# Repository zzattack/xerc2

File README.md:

Clone of XERC2 IR board for OG xbox.
Resembles original Sickmods design. Adds a programming header for the microcontroller.

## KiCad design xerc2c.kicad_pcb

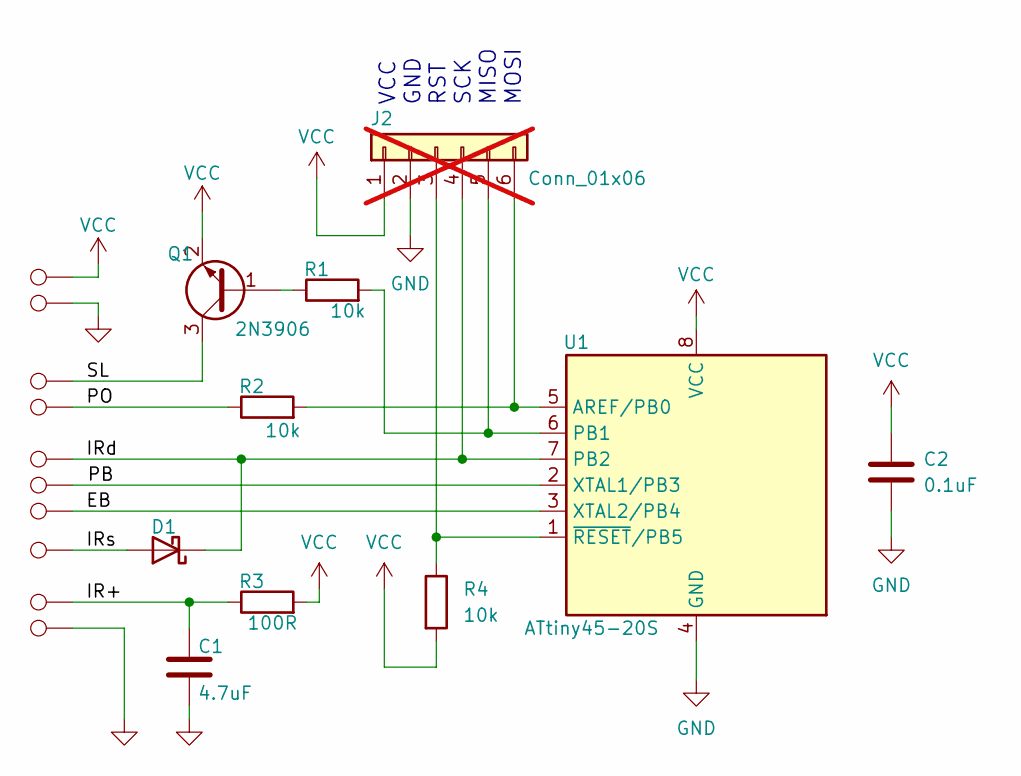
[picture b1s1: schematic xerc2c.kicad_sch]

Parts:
C1: 4.7uF; C_0805_2012Metric
C2: 0.1uF; C_0603_1608Metric
D1: D_Schottky; D_0603_1608Metric
J2: Conn_01x06; PinHeader_1x06_P2.54mm_Vertical; not fitted
Q1: 2N3906; SOT-23
R1, R2, R4: 10k; R_0603_1608Metric
R3: 100R; R_0603_1608Metric
TP1, TP2, TP3, TP4, TP5, TP6, TP7, TP8, TP9, TP10: SMD2; SMDPAD
U1: ATtiny45-20S; SOIC-8W_5.3x5.3mm_P1.27mm

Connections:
/EB: TP7.1, U1.3 (XTAL2/PB4)
/IR+: C1.1, R3.1, TP9.1
/IRd: D1.1 (K), J2.4, TP5.1, U1.7 (PB2)
/IRs: D1.2 (A), TP8.1
/PB: TP6.1, U1.2 (XTAL1/PB3)
/PO: R2.1, TP4.1
/SL: Q1.3 (C), TP3.1
GND: C1.2, C2.2, J2.2, TP2.1, TP10.1, U1.4 (GND)
unnamed: J2.3, R4.1, U1.1 (~RESET/PB5)
unnamed: J2.5, R1.2, U1.6 (PB1)
unnamed: J2.6, R2.2, U1.5 (AREF/PB0)
unnamed: Q1.1 (B), R1.1
VCC: C2.1, J2.1, Q1.2 (E), R3.2, R4.2, TP1.1, U1.8 (VCC)

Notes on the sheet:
VCC GND RST SCK MISO MOSI

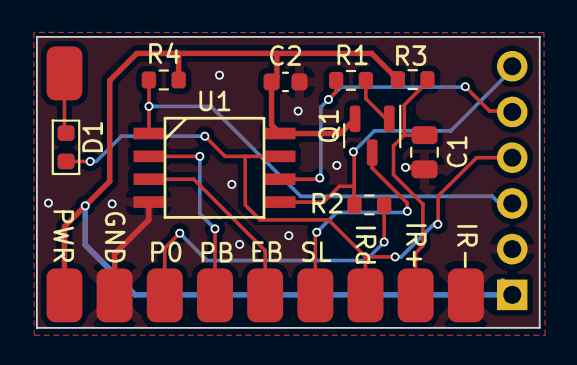
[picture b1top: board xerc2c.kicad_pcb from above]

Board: 2 copper layers, 27.9 x 16.2 mm, 20 parts (1 on the bottom side), 13 nets.

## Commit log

2024-02-26 Add KiCad files
